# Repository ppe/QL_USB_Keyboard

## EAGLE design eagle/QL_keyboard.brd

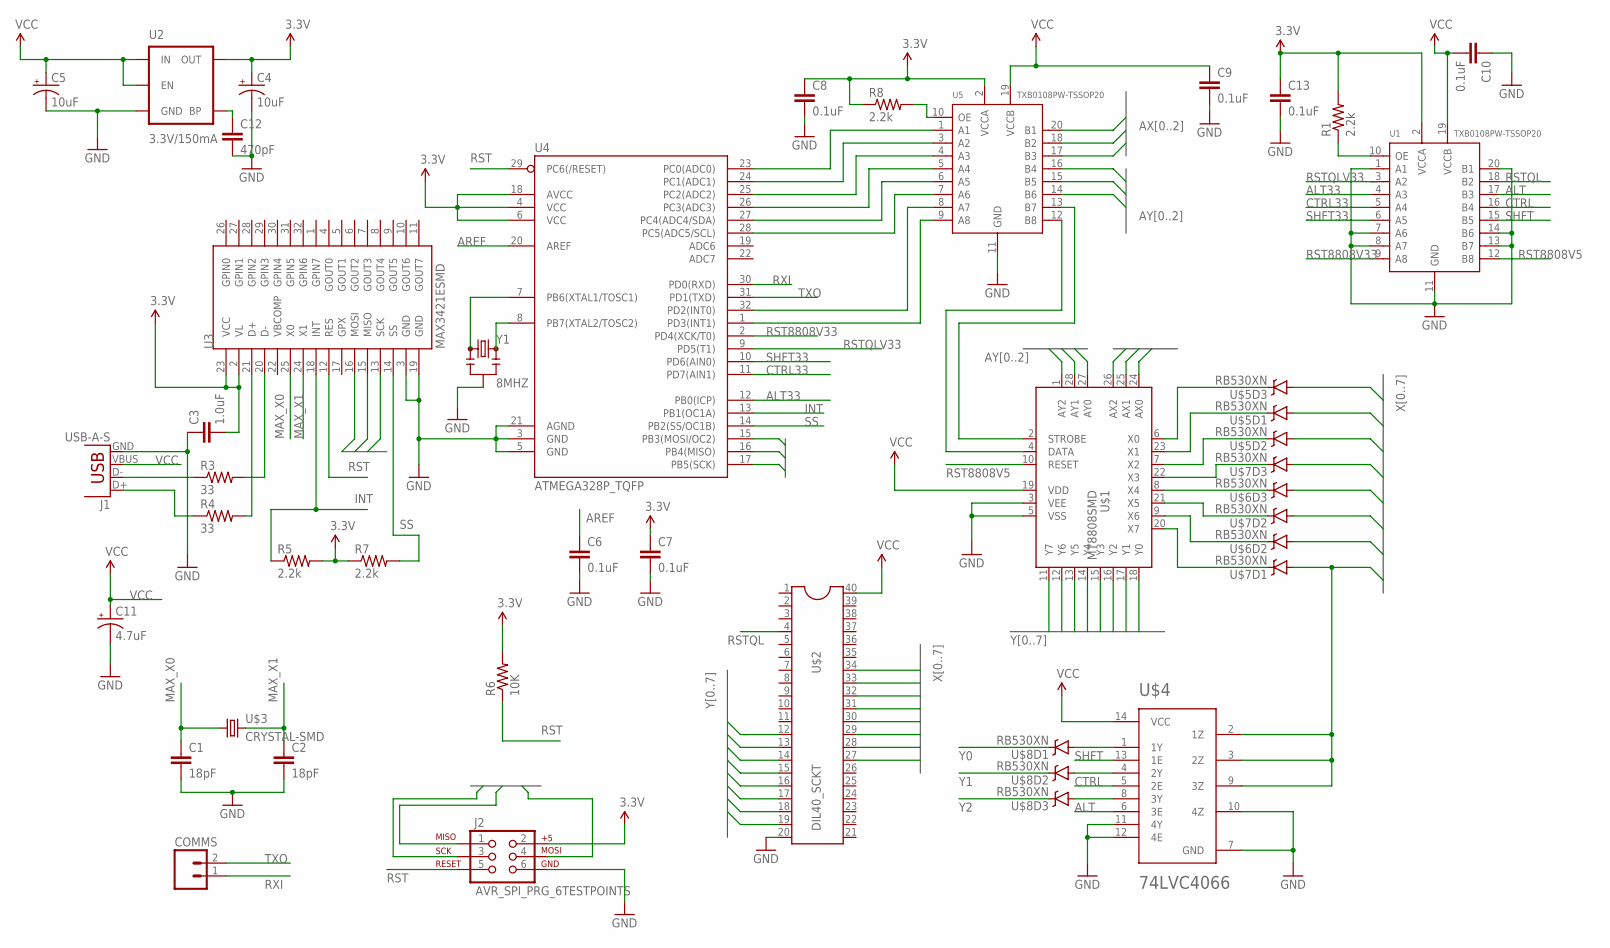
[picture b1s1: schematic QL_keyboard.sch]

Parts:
C1, C2: 18pF; 0603-CAP
C3: 1.0uF; 0603-CAP
C4, C5: 10uF; EIA3216
C6, C7, C8, C9, C10, C13: 0.1uF; 0603-CAP
C11: 4.7uF; 0603-POL
C12: 470pF; 0603-CAP
COMMS: M02PTH; 1X02
J1: USB-A-S
J2: AVR_SPI_PRG_6TESTPOINTS; 2X3_TEST_POINTS
R1, R5, R7, R8: 2.2k; 0603-RES
R3, R4: 33; 0603-RES
R6: 10K; 0603-RES
U1, U5: TXB0108PW-TSSOP20; TSSOP20-0.65-6.5X4.4MM
U2: 3.3V/150mA; SOT23-5
U3: MAX3421ESMD; TQFP32-5MM
U4: ATMEGA328P_TQFP; TQFP32-08
U$1: MT8808SMD; PLCC28S
U$2: DIL40_SCKT; DIL40
U$3: CRYSTAL-SMD; CRYSTAL-SMD-5X3.2
U$4: 74LVC4066; TSSOP14
U$5, U$6, U$7, U$8: RB530XN; SOT363
Y1: 8MHZ; RESONATOR-SMD

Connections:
3.3V: C3.2, C4.A (+), C7.1, C8.1, C13.1, J2.2, R1.2, R5.2, R6.2, R7.1, R8.1, U1.2 (VCCA), U2.5 (OUT), U3.2 (VL), U3.23 (VCC), U4.4 (VCC), U4.6 (VCC), U4.18 (AVCC), U5.2 (VCCA)
ALT: U1.17 (B3), U$4.6 (3E)
ALT33: U1.4 (A3), U4.12 (PB0(ICP))
AREF: C6.1, U4.20 (AREF)
AX0: U5.20 (B1), U$1.24 (AX0)
AX1: U5.18 (B2), U$1.25 (AX1)
AX2: U5.17 (B3), U$1.26 (AX2)
AY0: U5.16 (B4), U$1.27 (AY0)
AY1: U5.15 (B5), U$1.28 (AY1)
AY2: U5.14 (B6), U$1.1 (AY2)
CTRL: U1.16 (B4), U$4.5 (2E)
CTRL33: U1.5 (A4), U4.11 (PD7(AIN1))
GND: C1.2, C2.2, C3.1, C4.C (-), C5.C (-), C6.2, C7.2, C8.2, C9.2, C10.1, C11.K (-), C12.2, C13.2, J1.GND, J2.6, U1.1 (A1), U1.7 (A6), U1.8 (A7), U1.11 (GND), U1.13 (B7), U1.14 (B6), U1.20 (B1), U2.2 (GND), U3.3 (GND), U3.19 (GND), U4.3 (GND), U4.5 (GND), U4.21 (AGND), U5.11 (GND), U$1.3 (VEE), U$1.5 (VSS), U$2.20, U$4.7 (GND), U$4.10 (4Z), U$4.11 (4Y), U$4.12 (4E), Y1.2
INT: R5.1, U3.18 (INT), U4.13 (PB1(OC1A))
MAX_X0: C1.1, U3.25 (X0), U$3.1
MAX_X1: C2.1, U3.24 (X1), U$3.2
MISO: J2.1, U3.15 (MISO), U4.16 (PB4(MISO))
MOSI: J2.4, U3.16 (MOSI), U4.15 (PB3(MOSI/OC2))
unnamed: J1.D-, R3.1
unnamed: R3.2, U3.20 (D-)
unnamed: R4.2, U3.21 (D+)
unnamed: J1.D+, R4.1
unnamed: C12.1, U2.4 (BP)
unnamed: U4.23 (PC0(ADC0)), U5.1 (A1)
unnamed: U4.24 (PC1(ADC1)), U5.3 (A2)
unnamed: U4.25 (PC2(ADC2)), U5.4 (A3)
unnamed: U4.26 (PC3(ADC3)), U5.5 (A4)
unnamed: U4.27 (PC4(ADC4/SDA)), U5.6 (A5)
unnamed: U4.28 (PC5(ADC5/SCL)), U5.7 (A6)
unnamed: U4.32 (PD2(INT0)), U5.8 (A7)
unnamed: U5.12 (B8), U$1.4 (DATA)
unnamed: U5.13 (B7), U$1.2 (STROBE)
unnamed: U4.8 (PB7(XTAL2/TOSC2)), Y1.3
unnamed: U4.7 (PB6(XTAL1/TOSC1)), Y1.1
unnamed: R8.2, U5.10 (OE)
unnamed: U4.1 (PD3(INT1)), U5.9 (A8)
unnamed: U$1.6 (X0), U$5.3 (C)
unnamed: U$1.23 (X1), U$5.1 (C)
unnamed: U$1.7 (X2), U$5.2 (C)
unnamed: U$1.22 (X3), U$7.3 (C)
unnamed: U$1.8 (X4), U$6.3 (C)
unnamed: U$1.21 (X5), U$7.2 (C)
unnamed: U$1.9 (X6), U$6.2 (C)
unnamed: U$1.20 (X7), U$7.1 (C)
unnamed: U$4.1 (1Y), U$8.6 (A)
unnamed: U$4.4 (2Y), U$8.5 (A)
unnamed: U$4.8 (3Y), U$8.4 (A)
unnamed: R1.1, U1.10 (OE)
RST: J2.5, R6.1, U3.12 (RES), U4.29 (PC6(/RESET))
RST8808V5: U1.12 (B8), U$1.10 (RESET)
RST8808V33: U1.9 (A8), U4.2 (PD4(XCK/T0))
RSTQL: U1.18 (B2), U$2.4
RSTQLV33: U4.9 (PD5(T1))
RXI: COMMS.1, U4.30 (PD0(RXD))
SCK: J2.3, U3.13 (SCK), U4.17 (PB5(SCK))
SHFT: U1.15 (B5), U$4.13 (1E)
SHFT33: U1.6 (A5), U4.10 (PD6(AIN0))
SS: R7.2, U3.14 (SS), U4.14 (PB2(SS/OC1B))
TXO: COMMS.2, U4.31 (PD1(TXD))
VCC: C5.A (+), C9.1, C10.2, C11.A (+), J1.VBUS, U1.19 (VCCB), U2.1 (IN), U2.3 (EN), U5.19 (VCCB), U$1.19 (VDD), U$2.40, U$4.14 (VCC)
X0: U$2.27, U$5.4 (A)
X1: U$2.28, U$5.6 (A)
X2: U$2.29, U$5.5 (A)
X3: U$2.30, U$7.4 (A)
X4: U$2.31, U$6.4 (A)
X5: U$2.32, U$7.5 (A)
X6: U$2.33, U$6.5 (A)
X7: U$2.34, U$4.2 (1Z), U$4.3 (2Z), U$4.9 (3Z), U$7.6 (A)
Y0: U$1.18 (Y0), U$2.12, U$8.1 (C)
Y1: U$1.17 (Y1), U$2.13, U$8.2 (C)
Y2: U$1.16 (Y2), U$2.14, U$8.3 (C)
Y3: U$1.15 (Y3), U$2.15
Y4: U$1.14 (Y4), U$2.16
Y5: U$1.13 (Y5), U$2.17
Y6: U$1.12 (Y6), U$2.18
Y7: U$1.11 (Y7), U$2.19

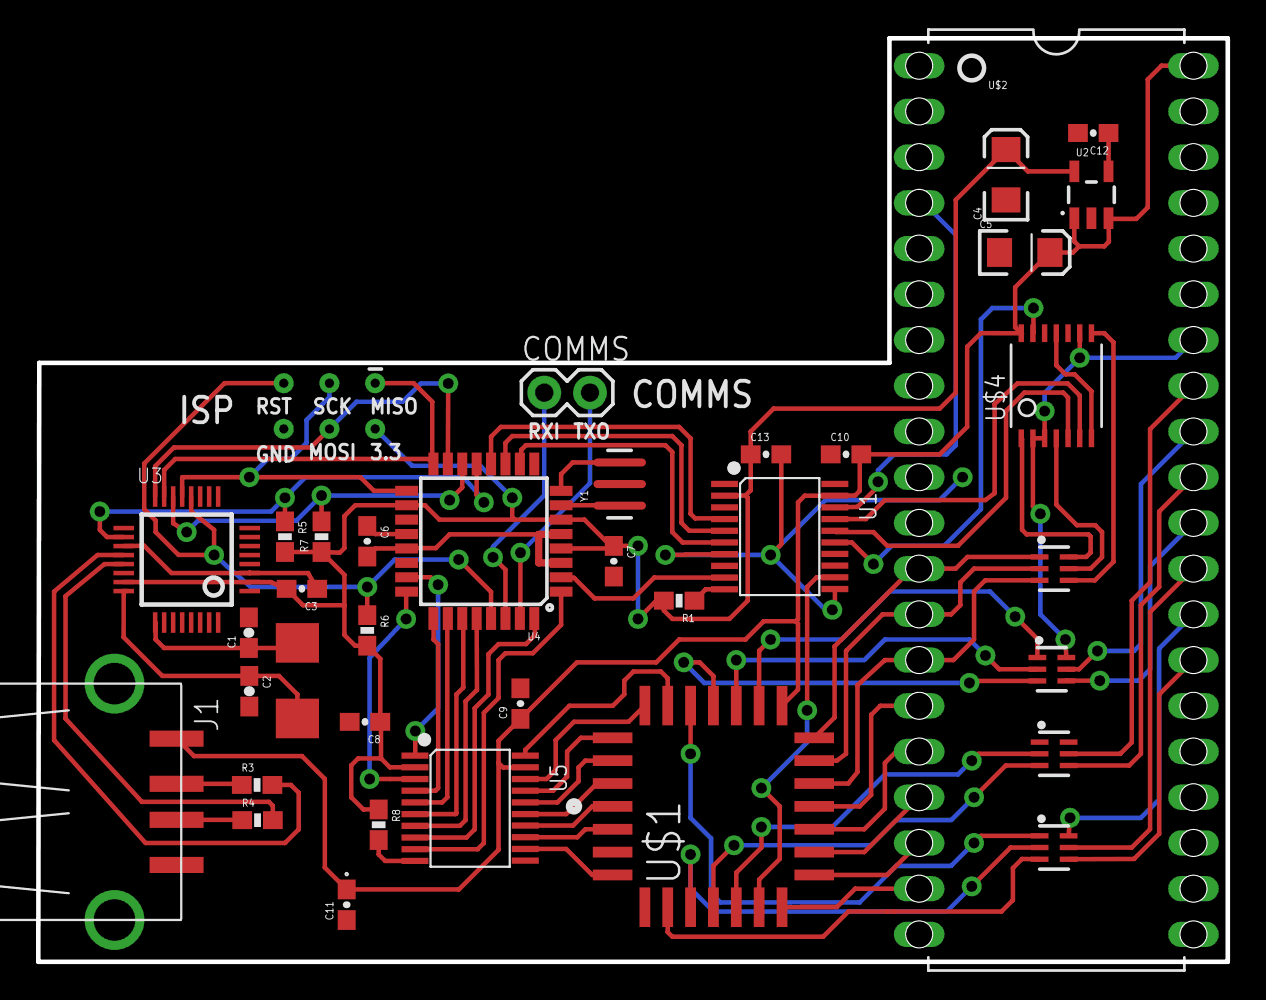
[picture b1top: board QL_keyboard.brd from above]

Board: 2 copper layers, 66.1 x 51.3 mm, 37 parts (0 on the bottom side), 75 nets.

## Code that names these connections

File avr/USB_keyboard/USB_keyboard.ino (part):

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#include <SPI.h>
#endif

// PD0 == RXI point on board edge
// PD1 == TXO point on board edge
// Can run soft serial on these for debugging purposes

// Strobe is used to clock gate changes to the 8808 switch matrix
const byte strobe = PD2;
// Data is the state of the switch matrix switch to set (1==closed, 0==open)
const byte data = PD3;
// Resets the 8808 switch matrix (all switches off)
const byte reset = PD4;

// Pin that is connected to the QL resetLow line
// Not used at the moment, needs HW review
// const byte resetQL = PD5;

// Pin to control modifier keys that are implemented using the separate 74LVC4066 quad switch IC
const byte shift = PD6;
const byte ctrl = PD7;
const byte alt = PB0;

/*
 * USB keycode to switch matrix address translation table
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 * 0xFF == not mapped
 * 0b10xxxxxx will be looked up in the specialKeys table below that represent combination key presses on the QL
 * e.g. 0x81 maps to PC keyboard Del to specialKeys row 1, or ctrl-right on the QL
 * 0x40 will be looked up in the pcToQlMapping table to support mapping, e.g. ctrl-2 on PC to ï on QL
 * currently hardcoded to only supporet "2" key mapping for testing purposes
 */
const byte keyMapping[83] = {
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  // TODO currently only one possible mapping (used for "2" key)
  // TODO should probbaly use logic similar to specialKeys where row selected based on mapping table above
  // i.e. 0x40 == row 0, 0x41 == row 1, etc.
  // Mapping for USB event modifiers {Plain, Shift, Ctrl, Shift-Ctrl, AltGr}
  // Value in table -> Bit 7 controls ctrl-key on QL side, Bit 6 controls alt-key on QL side
  // 2 == 2, Shift-2(") == Shift-', Ctrl-2 == ï (orig), Shift-Ctrl-2 == Ä (mapped elsewhere), , AltGr-2 (@) == Shift-2
  // e.g. mapping of shift-2 to 0x7A (01 111 100) will activate shift modifier on QL and switch on matrix address 111 100
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// Would need to check first that there aren't multiple outputs connected together on the PCB
//  pinMode( resetQL, OUTPUT);
  pinMode( shift, OUTPUT);
  pinMode( ctrl, OUTPUT);
  pinMode( alt, OUTPUT);
  digitalWrite( reset, HIGH );
  digitalWrite( reset, LOW );
  digitalWrite( data, LOW );
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  digitalWrite( alt, LOW );
  
  DDRC |= 0x3F; // Set C0-C5 to be output - these are the 8808 switch matrix address selection pins
  PCMSK2 |= 0b00000001; // PCINT16, watch changes on PD0

// I have absolutely no idea why this code is here
// reset above should clear all the switch states, according to datasheet
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
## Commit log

2016-02-26 First layout version
2016-02-26 Add temp files to ignore
2016-02-26 WIP test atmega rotation
2016-02-26 WIP second layout version
2016-02-26 Second, more compact, version of board.
2016-02-26 Add bottom silk screen text.
2016-02-26 Parameterize CAM job to use name of board in files.
2016-02-26 Add gerber files to ignore
2016-02-26 Move Eagle files to own directory
2016-02-26 Add atmega driver
2016-02-26 Add github info on bottom silk.
2016-02-26 Move trace near edge of board
2016-02-26 Move diodes out of the way of DIL socket frame
2016-03-05 Change pin/port mappings to match revised hardware
2016-03-21 Fix bug in MT8808 VEE connection: connect to GND instead of VCC
2016-03-21 Minor layout change
2016-03-26 Change MT8808 package to SMD PLCC28 holder.
2016-03-26 Replace FTDI header with a two pin RXI/TXO header.
2016-03-26 Move ISP header and fix USB connector footprint
2016-03-26 General cleanup of layout
2016-03-28 Add QL reset logic with voltage level shifting.
2016-04-02 Minor routing adjustments
2016-04-02 Change gitignore so that Gerber files are also tracked
2016-04-02 Add rendered Gerber files to project
2016-05-03 Minor routing change in board.
2021-10-06 WIP: experimenting with mouse support
2021-10-06 WIP: support key combinations and pc to ql mappings
2021-10-06 Add comment about probable bug

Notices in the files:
eagle/QL_keyboard.brd:
(c) 2016 Petri Pellinen
parts and their libraries:
SparkFun-DiscreteSemi: Licensing: Creative Commons ShareAlike 4.0 International - https://creativecommons.org/licenses/by-sa/4.0
